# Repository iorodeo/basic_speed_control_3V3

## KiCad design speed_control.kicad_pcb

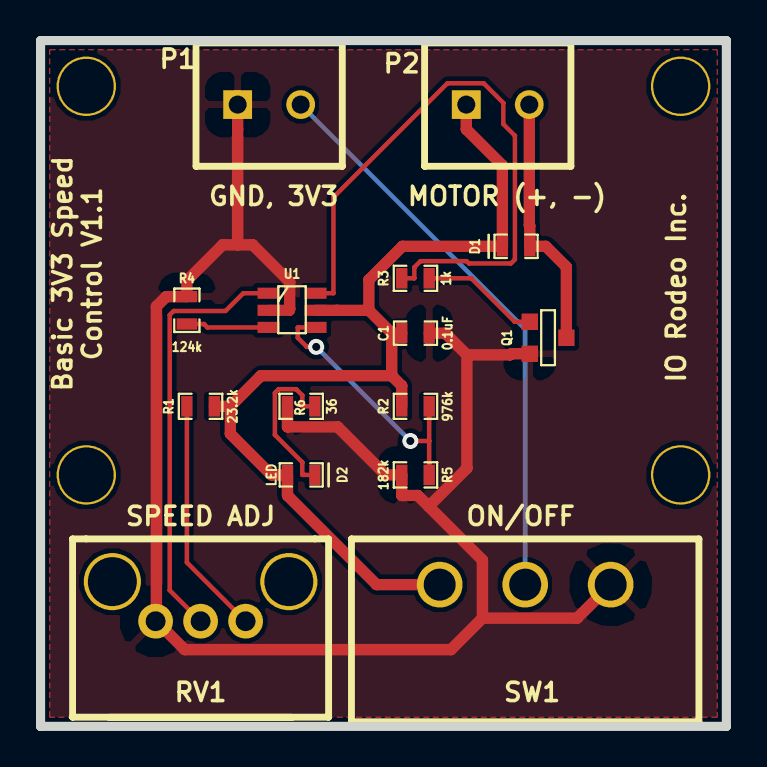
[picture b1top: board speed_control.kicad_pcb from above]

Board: 2 copper layers, 38.1 x 38.1 mm, 19 parts (0 on the bottom side), 11 nets.

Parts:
C1: 0.1uF; SM0603_Capa
D1: DIODESCH; SM0603_Diode
D2: LED; SM0603_Diode
M1, M2, M3, M4: VAL**; MOUNT_HOLE_4_40
P1, P2: CONN_2; BLOCK_CONN_2X1
Q1: NPN; SOT23EBC
R1: 23.2k; SM0603_Resistor
R2: 976k; SM0603_Resistor
R3: 1k; SM0603_Resistor
R4: 124k; SM0603_Resistor
R5: 182k; SM0603_Resistor
R6: 36; SM0603_Resistor
RV1: 10k; POT_EVUE2J
SW1: SWITCH_INV; SLIDE_SWITCH
U1: LTC6992_TSOT_32_6; SOT23_6_CUSTOM

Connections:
+3.3V: C1.1, D1.2, D2.1, P2.1, R1.1, R2.1, SW1.1, U1.5
GND: C1.2, P1.1, Q1.1, R4.2, R5.2, R6.2, RV1.1, SW1.3, U1.2
unnamed: P1.2, SW1.2
unnamed: Q1.2, R3.1
unnamed: D1.1, P2.2, Q1.3
unnamed: D2.2, R6.1
unnamed: RV1.2, U1.1
unnamed: R4.1, U1.3
unnamed: R1.2, RV1.3
unnamed: R3.2, U1.6
unnamed: R2.2, R5.1, U1.4

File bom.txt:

Part     Description                  Package     Vendor    Part Number
----     -----------                  -------     ------    -----------
C1       capacitor   0.1uF            SM0603      Digikey   1276-1258-1-ND
D1       diode, schottky (fast resp)  SM0603      Digikey   641-1332-1-ND 
D2       led blue (2.8Vf)             SM0603      Digikey   160-1827-1-ND
P1       terminal block, 3.5mm vert   custom      Digikey   ED2635-ND 
P2       terminal block, 3.5mm vert   custom      Digikey   ED2635-ND 
Q1       npn transistor               SOT-23-3    Digieky   FMMT619CT-ND
R1       resistor    23.2k            SM0603      Digikey   P23.2KHCT-ND
R2       resistor    976k             SM0603      Digikey   RMCF0603FT976KCT-ND
R3       resistor    1k               SM0603      Digikey   RMCF0603JT1K00CT-ND
R4       resistor    124k             SM0603      Digikey   311-124KDCT-ND
R5       resistor    182k             SMO603      Digikey   541-182KHCT-ND 
R6       resistor    36               SM0603      Digikey   311-36GRCT-ND
RV1      potentiometer 10k            custom      Digikey   P3T9103-ND
SW1      switch, slide, spdt          custom      Digikey   CKC5102-ND
U1       Voltage controlled PWM       TSOT-23-6   Digikey   LTC6992CS6-1#TRMPBFCT-ND

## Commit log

2013-12-04 Project creation.
2013-12-04 Added license.
2014-01-23 Added trace to PWR class and re-routed. Created gerber files for version 1.1.
2014-02-10 Flipped potentiometer so direction of rotation is typical (as opposed to reverse). Added indicator LED. Re-routed.
2014-04-12 Modified schematic so that page size is us letter. Added pdf of schematic.
